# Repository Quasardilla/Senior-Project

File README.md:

# Haptic Feedback Remote
This "remote" is a design concept that utilizes a touchpad as opposed to a D-pad with the intention to control a tv (although this concept doesn't include any of the hardware required for communication). Based on inputs, the remote will vibrate in specific patterns (haptic feedback) in order to simulate certain feelings like a click or a scroll. 

# Features
Click: When the touchpad is pressed and released, the voice coil will give a kick accompanied by a little chirp

Scroll: When the touchpad is pressed and moved across, the voice coil gives a very light kick for every movement in the X or Y direction

Simulated Scroll: When the touchpad is being scrolled across, and the user lets go, the micro calculates how often a scroll click should happen given the velocity of the movement before it was released. The voice coil reacts as though it's scrolling from an actual interaction

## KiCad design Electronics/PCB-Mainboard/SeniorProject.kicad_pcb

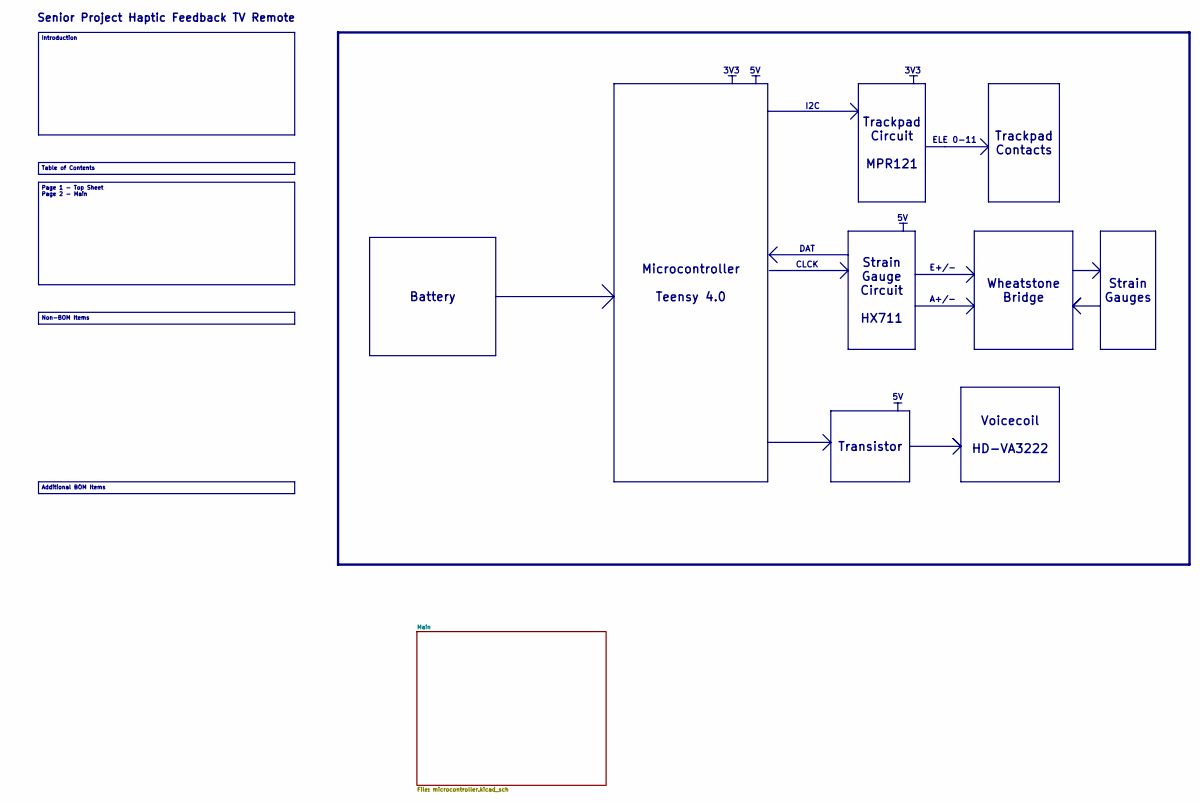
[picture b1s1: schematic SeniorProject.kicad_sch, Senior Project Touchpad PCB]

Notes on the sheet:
A+/-
CLCK
ELE 0-11
3V3
I2C
E+/-
Senior Project Haptic Feedback TV Remote
DAT
Table of Contents
Battery
Transistor
Trackpad Contacts
Voicecoil HD-VA3222
Introduction
Microcontroller Teensy 4.0
Page 1 - Top Sheet Page 2 - Main
Wheatstone Bridge
Additional BOM Items
Trackpad Circuit MPR121
Strain Gauges
Strain Gauge Circuit HX711
Non-BOM Items

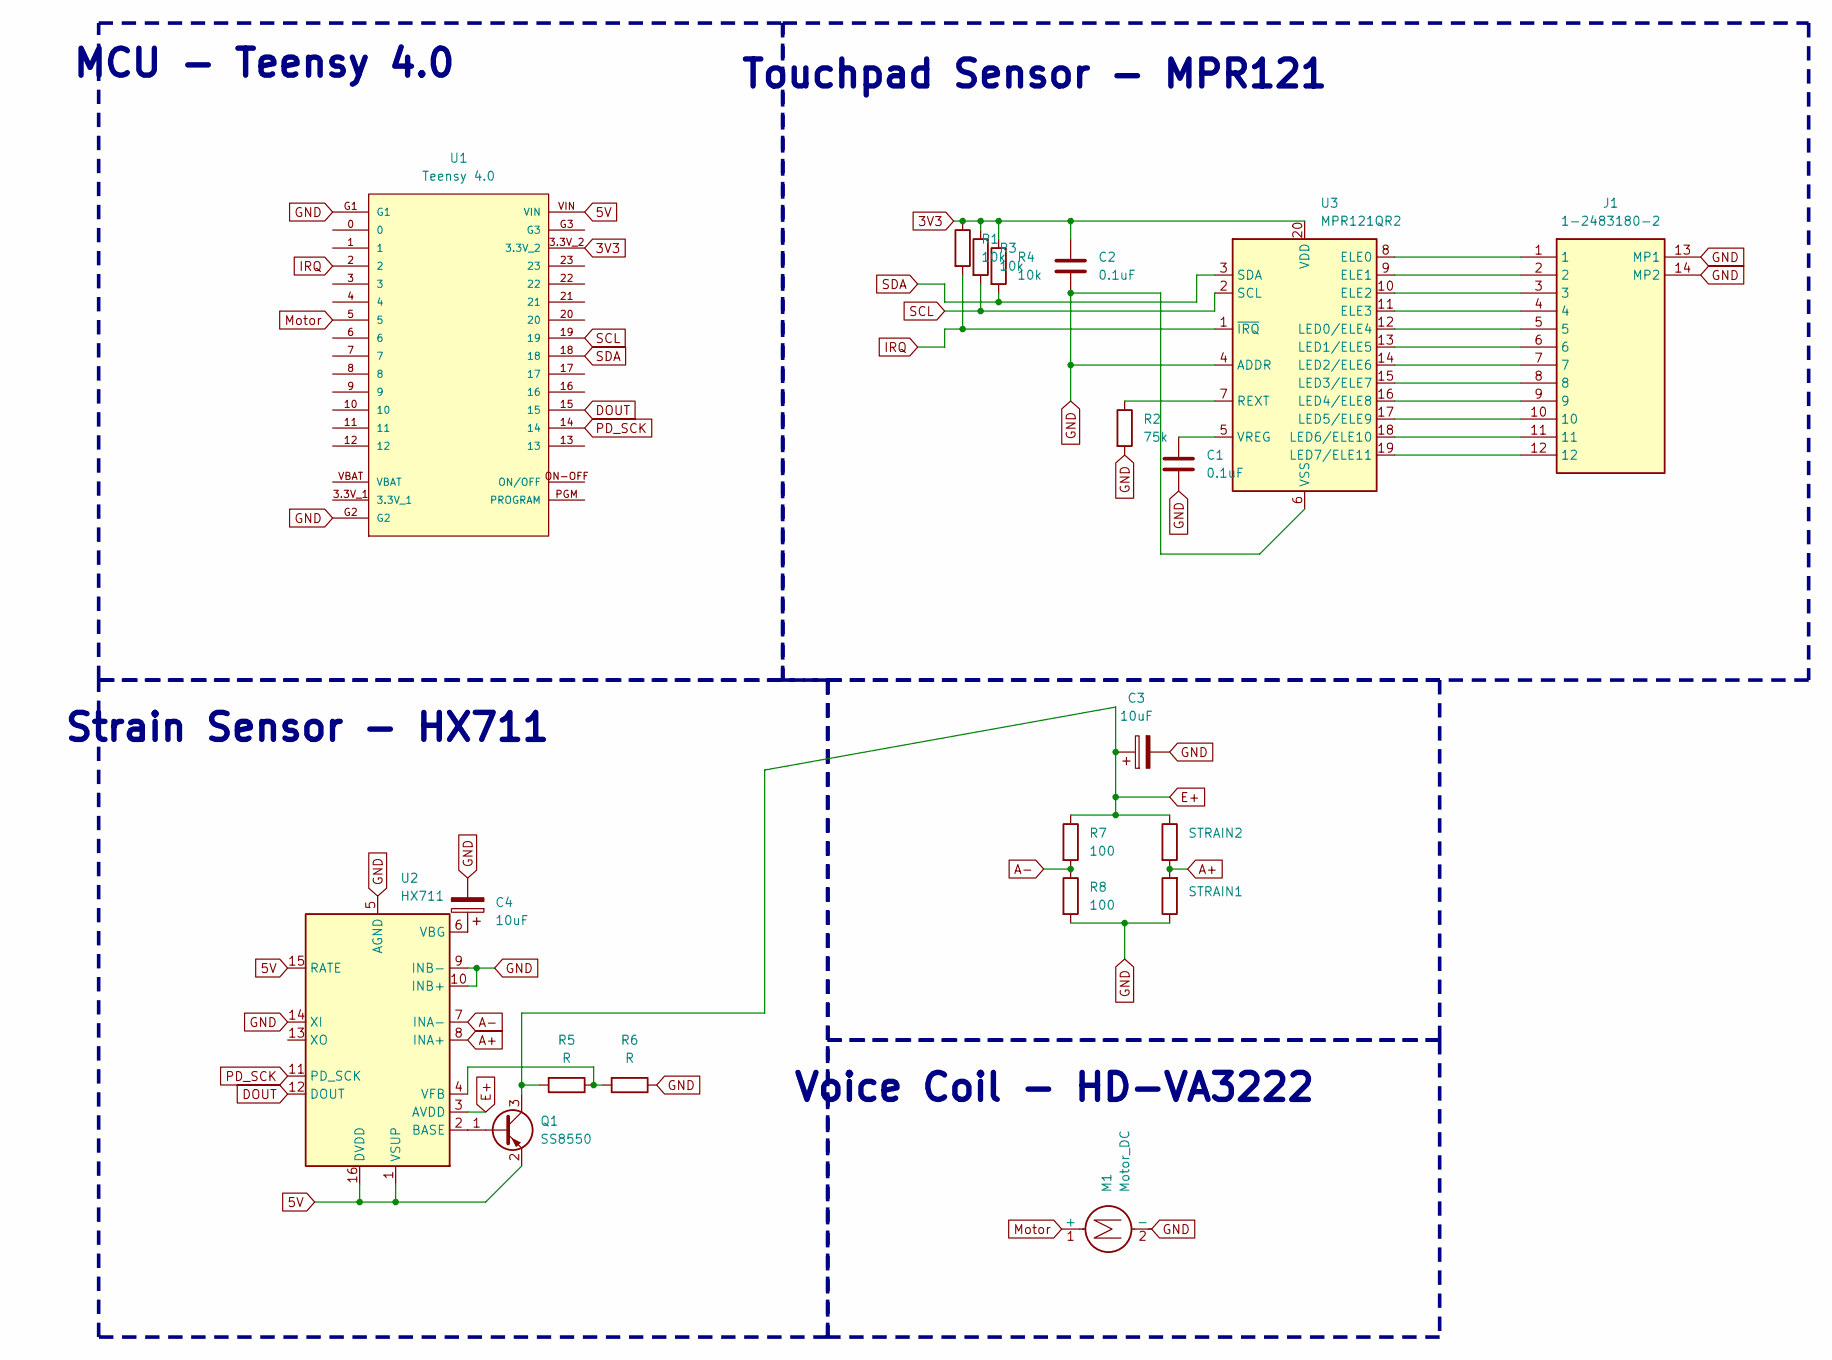
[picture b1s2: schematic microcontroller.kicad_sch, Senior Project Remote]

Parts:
C1, C2: 0.1uF; C_0201_0603Metric
C3, C4: 10uF; CP_Elec_4x4.5
J1: 1-2483180-2; Manufacturer_Part_Number 1-2483180-2; Mouser Part Number 571-1-2483180-2
M1: Motor_DC; R_2816_7142Metric_Pad3.20x4.45mm_HandSolder
Q1: SS8550; SOT-416
R1, R3, R4: 10k; R_0201_0603Metric
R2: 75k; R_0201_0603Metric
R5, R6: R; R_0201_0603Metric
R7, R8: 100; R_0201_0603Metric
STRAIN1, STRAIN2: R_2816_7142Metric_Pad3.20x4.45mm_HandSolder
U1: Teensy 4.0; MODULE_Teensy 4.0
U2: HX711; SOP-16_3.9x9.9mm_P1.27mm
U3: MPR121QR2; UQFN-20_3x3mm_P0.4mm

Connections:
3V3: C2.1, R1.1, R3.1, R4.1, U1.3.3V_2, U3.20 (VDD)
5V: Q1.2 (E), U1.VIN, U2.1 (VSUP), U2.15 (RATE), U2.16 (DVDD)
A+: STRAIN1.2, STRAIN2.2, U2.8 (INA+)
A-: R7.2, R8.1, U2.7 (INA-)
DOUT: U1.15, U2.12 (DOUT)
E+: C3.1, Q1.3 (C), R5.2, R7.1, STRAIN2.1, U2.3 (AVDD)
IRQ: R1.2, U1.2, U3.1 (~IRQ)
unnamed: Q1.1 (B), U2.2 (BASE)
unnamed: C4.1, U2.6 (VBG)
unnamed: R5.1, R6.2, U2.4 (VFB)
unnamed: J1.1, U3.8 (ELE0)
unnamed: J1.2, U3.9 (ELE1)
unnamed: J1.3, U3.10 (ELE2)
unnamed: J1.4, U3.11 (ELE3)
unnamed: J1.5, U3.12 (LED0/ELE4)
unnamed: J1.6, U3.13 (LED1/ELE5)
unnamed: J1.7, U3.14 (LED2/ELE6)
unnamed: J1.8, U3.15 (LED3/ELE7)
unnamed: J1.9, U3.16 (LED4/ELE8)
unnamed: J1.10, U3.17 (LED5/ELE9)
unnamed: J1.11, U3.18 (LED6/ELE10)
unnamed: J1.12, U3.19 (LED7/ELE11)
unnamed: R2.1, U3.7 (REXT)
unnamed: C1.1, U3.5 (VREG)
PD_SCK: U1.14, U2.11 (PD_SCK)
SCL: R3.2, U1.19, U3.2 (SCL)
SDA: R4.2, U1.18, U3.3 (SDA)

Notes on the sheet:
Touchpad Sensor - MPR121
MCU - Teensy 4.0
Strain Sensor - HX711
Voice Coil - HD-VA3222

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
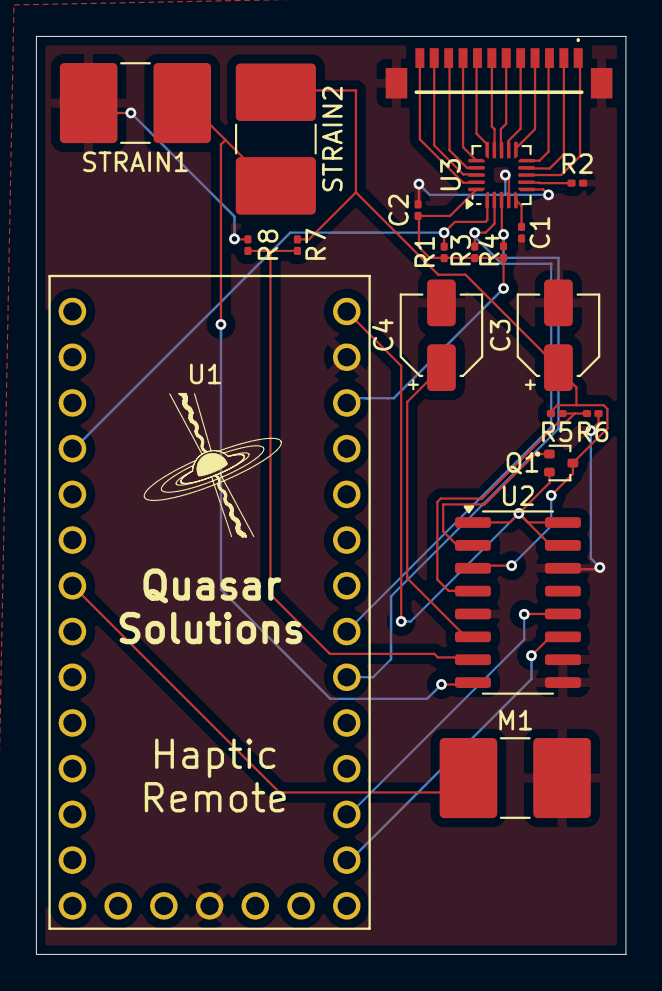
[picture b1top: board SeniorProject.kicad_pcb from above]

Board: 2 copper layers, 32.8 x 51.0 mm, 20 parts (0 on the bottom side), 29 nets.

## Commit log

2025-05-29 Simulated Scrolling stuff
2025-05-29 sim pose
2025-05-29 Finished product (for now)
    Flick-scrolling works now!!!
    Lots of comments added
2025-06-21 PCBs and Organization
2025-06-21 read me's
